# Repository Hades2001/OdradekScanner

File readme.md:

# Odradek Scanner
[中文](./readme_zh.md) | 英文

A 3D-printed Odradek Scanner project.

## Introduction

**Odradek Scanner** is a 3D-printed project inspired by the iconic scanner device.  
This repository is used to organize and publish the hardware resources, controller firmware, and related documentation required to build the project.

The goal of this project is not only to recreate its appearance, but also to turn it into a truly interactive Maker project that can be assembled, operated, and further expanded.

## Features

- Odradek-style 3D-printed structure
- Open-source hardware resources
- Controller firmware source code
- Project documentation including assembly manual and BOM
- Easy to organize, expand, and customize

## Repository Structure

.
├── Hardware/   # Open-source hardware files
├── Firmware/   # Controller firmware source code
├── Mechanical/ # Mechanical structure files
└── Docs/       # Assembly manual, BOM, and related documents

## Documentation

All project-related documentation will be organized in the `Docs/` directory, including:

* Assembly instructions
* BOM
* Wiring information
* User guide
* Additional reference materials

## Open Source

This project will continue to be organized and shared as an open-source Maker project.  
You are welcome to study it, build it, modify it, and further improve or expand it.

## Contribution

Suggestions, improvements, and additional content are always welcome.  
If you build your own version or improve the project, feel free to share your work.

## License

* [Hardware: CERN-OHL-P-2.0](./LICENSE/LICENSE-CERN-OHL-P-2.0.txt)
* [Firmware: MIT](./LICENSE/LICENSE-MIT.txt)
* [Documentation: CC BY 4.0](./LICENSE/LICENSE-CC-BY-4.0.txt)

## Notes

This repository will continue to be updated and expanded over time, with more files and documentation added gradually.

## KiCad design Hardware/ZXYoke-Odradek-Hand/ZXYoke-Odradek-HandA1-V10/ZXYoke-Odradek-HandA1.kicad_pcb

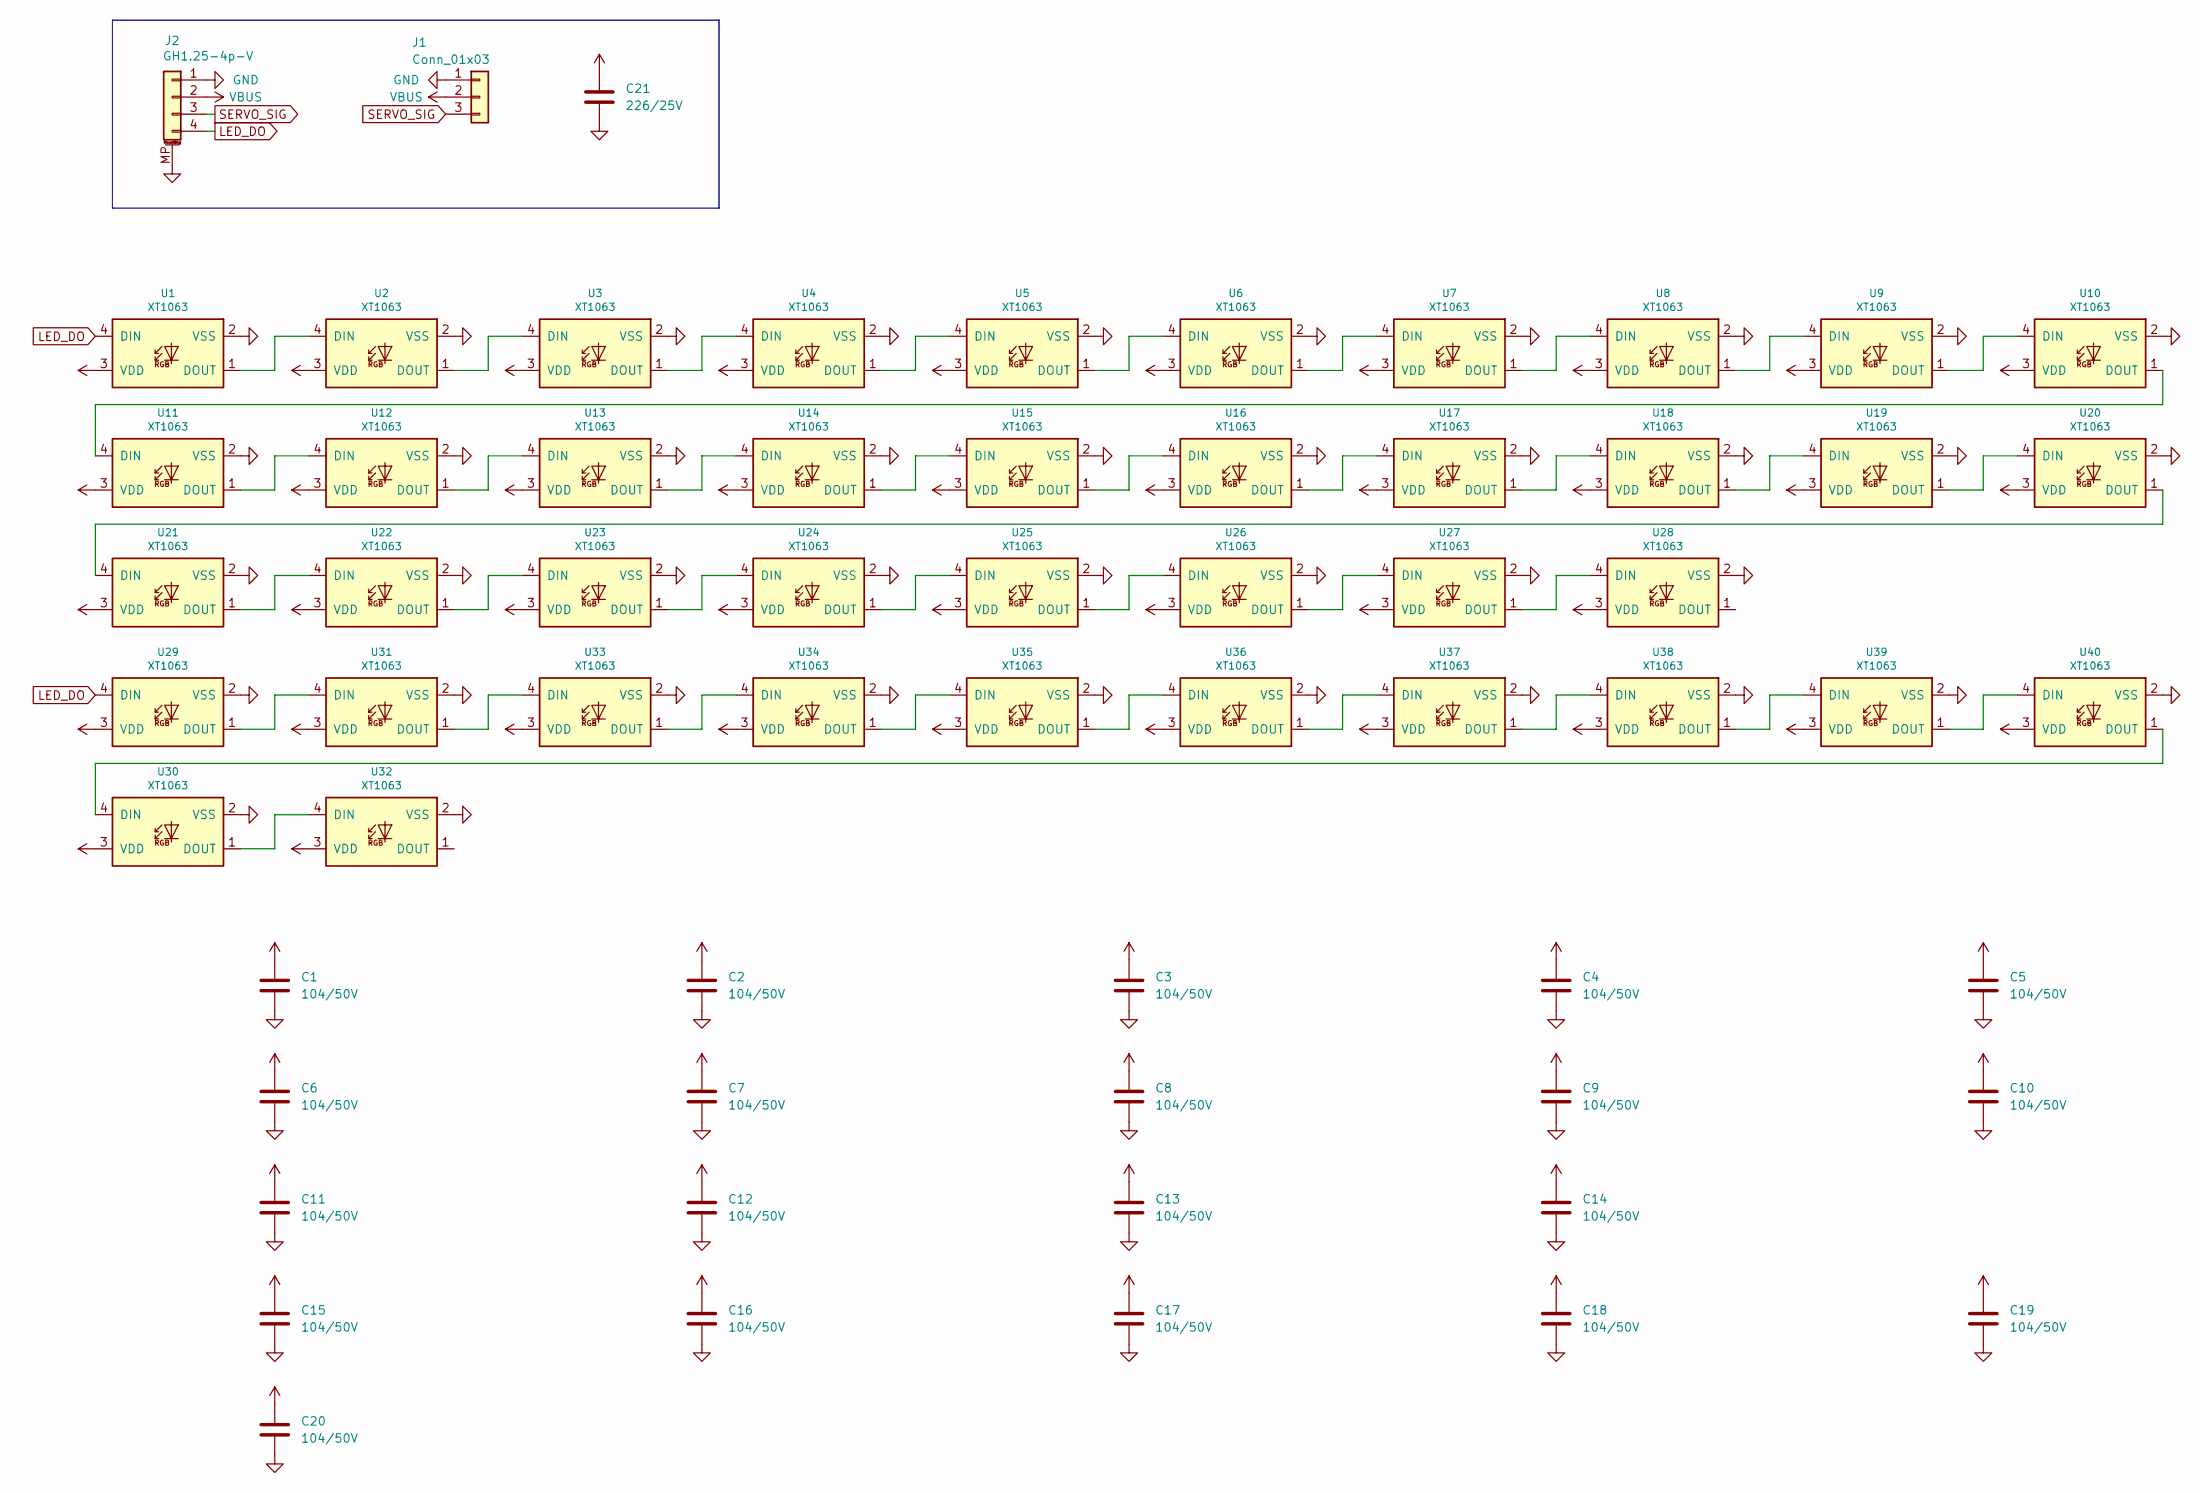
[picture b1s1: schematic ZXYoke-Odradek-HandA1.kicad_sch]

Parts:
C1, C2, C3, C4, C5, C6, C7, C8, C9, C10, C11, C12, C13, C14, C15, C16, C17, C18, C19, C20: 104/50V; C_0402_1005Metric
C21: 226/25V; C_0805_2012Metric
J1: Conn_01x03; PinHeader_1x03_P2.54mm_Horizontal
J2: GH1.25-4p-V; JST_GH_BM04B-GHS-TBT_1x04-1MP_P1.25mm_Vertical
U1, U2, U3, U4, U5, U6, U7, U8, U9, U10, U11, U12, U13, U14, U15, U16, U17, U18, U19, U20, U21, U22, U23, U24, U25, U26, U27, U28, U29, U30, U31, U32, U33, U34, U35, U36, U37, U38, U39, U40: XT1063

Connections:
GND: C1.2, C2.2, C3.2, C4.2, C5.2, C6.2, C7.2, C8.2, C9.2, C10.2, C11.2, C12.2, C13.2, C14.2, C15.2, C16.2, C17.2, C18.2, C19.2, C20.2, C21.2, J1.1, J2.1, J2.MP (MountPin), U1.2 (VSS), U2.2 (VSS), U3.2 (VSS), U4.2 (VSS), U5.2 (VSS), U6.2 (VSS), U7.2 (VSS), U8.2 (VSS), U9.2 (VSS), U10.2 (VSS), U11.2 (VSS), U12.2 (VSS), U13.2 (VSS), U14.2 (VSS), U15.2 (VSS), U16.2 (VSS), U17.2 (VSS), U18.2 (VSS), U19.2 (VSS), U20.2 (VSS), U21.2 (VSS), U22.2 (VSS), U23.2 (VSS), U24.2 (VSS), U25.2 (VSS), U26.2 (VSS), U27.2 (VSS), U28.2 (VSS), U29.2 (VSS), U30.2 (VSS), U31.2 (VSS), U32.2 (VSS), U33.2 (VSS), U34.2 (VSS), U35.2 (VSS), U36.2 (VSS), U37.2 (VSS), U38.2 (VSS), U39.2 (VSS), U40.2 (VSS)
LED_DO: J2.4, U1.4 (DIN), U29.4 (DIN)
unnamed: U1.1 (DOUT), U2.4 (DIN)
unnamed: U2.1 (DOUT), U3.4 (DIN)
unnamed: U3.1 (DOUT), U4.4 (DIN)
unnamed: U4.1 (DOUT), U5.4 (DIN)
unnamed: U5.1 (DOUT), U6.4 (DIN)
unnamed: U6.1 (DOUT), U7.4 (DIN)
unnamed: U7.1 (DOUT), U8.4 (DIN)
unnamed: U8.1 (DOUT), U9.4 (DIN)
unnamed: U9.1 (DOUT), U10.4 (DIN)
unnamed: U10.1 (DOUT), U11.4 (DIN)
unnamed: U11.1 (DOUT), U12.4 (DIN)
unnamed: U12.1 (DOUT), U13.4 (DIN)
unnamed: U13.1 (DOUT), U14.4 (DIN)
unnamed: U14.1 (DOUT), U15.4 (DIN)
unnamed: U15.1 (DOUT), U16.4 (DIN)
unnamed: U16.1 (DOUT), U17.4 (DIN)
unnamed: U17.1 (DOUT), U18.4 (DIN)
unnamed: U18.1 (DOUT), U19.4 (DIN)
unnamed: U19.1 (DOUT), U20.4 (DIN)
unnamed: U20.1 (DOUT), U21.4 (DIN)
unnamed: U21.1 (DOUT), U22.4 (DIN)
unnamed: U22.1 (DOUT), U23.4 (DIN)
unnamed: U23.1 (DOUT), U24.4 (DIN)
unnamed: U24.1 (DOUT), U25.4 (DIN)
unnamed: U25.1 (DOUT), U26.4 (DIN)
unnamed: U26.1 (DOUT), U27.4 (DIN)
unnamed: U27.1 (DOUT), U28.4 (DIN)
unnamed: U29.1 (DOUT), U31.4 (DIN)
unnamed: U30.4 (DIN), U40.1 (DOUT)
unnamed: U30.1 (DOUT), U32.4 (DIN)
unnamed: U31.1 (DOUT), U33.4 (DIN)
unnamed: U33.1 (DOUT), U34.4 (DIN)
unnamed: U34.1 (DOUT), U35.4 (DIN)
unnamed: U35.1 (DOUT), U36.4 (DIN)
unnamed: U36.1 (DOUT), U37.4 (DIN)
unnamed: U37.1 (DOUT), U38.4 (DIN)
unnamed: U38.1 (DOUT), U39.4 (DIN)
unnamed: U39.1 (DOUT), U40.4 (DIN)
SERVO_SIG: J1.3, J2.3
VBUS: C1.1, C2.1, C3.1, C4.1, C5.1, C6.1, C7.1, C8.1, C9.1, C10.1, C11.1, C12.1, C13.1, C14.1, C15.1, C16.1, C17.1, C18.1, C19.1, C20.1, C21.1, J1.2, J2.2, U1.3 (VDD), U2.3 (VDD), U3.3 (VDD), U4.3 (VDD), U5.3 (VDD), U6.3 (VDD), U7.3 (VDD), U8.3 (VDD), U9.3 (VDD), U10.3 (VDD), U11.3 (VDD), U12.3 (VDD), U13.3 (VDD), U14.3 (VDD), U15.3 (VDD), U16.3 (VDD), U17.3 (VDD), U18.3 (VDD), U19.3 (VDD), U20.3 (VDD), U21.3 (VDD), U22.3 (VDD), U23.3 (VDD), U24.3 (VDD), U25.3 (VDD), U26.3 (VDD), U27.3 (VDD), U28.3 (VDD), U29.3 (VDD), U30.3 (VDD), U31.3 (VDD), U32.3 (VDD), U33.3 (VDD), U34.3 (VDD), U35.3 (VDD), U36.3 (VDD), U37.3 (VDD), U38.3 (VDD), U39.3 (VDD), U40.3 (VDD)

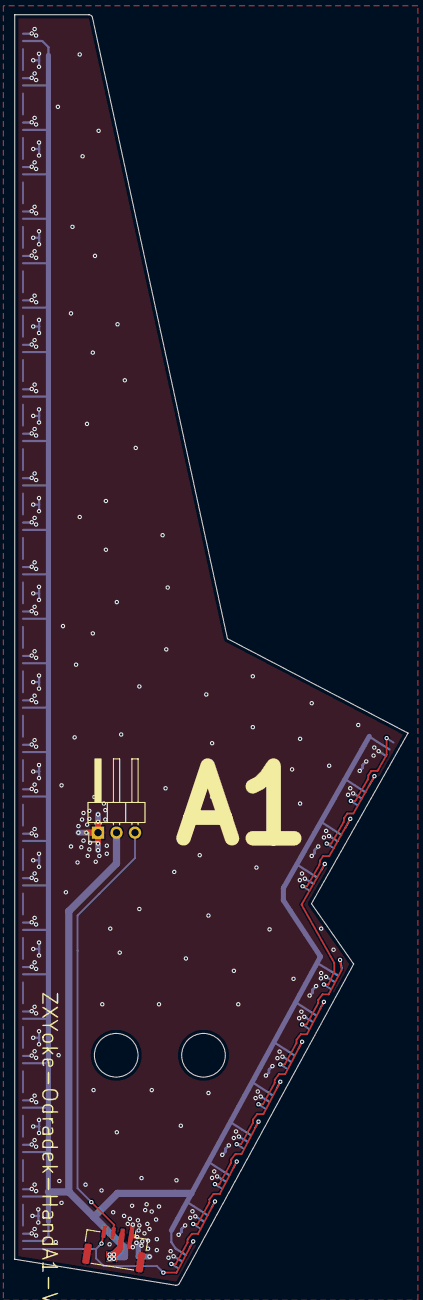
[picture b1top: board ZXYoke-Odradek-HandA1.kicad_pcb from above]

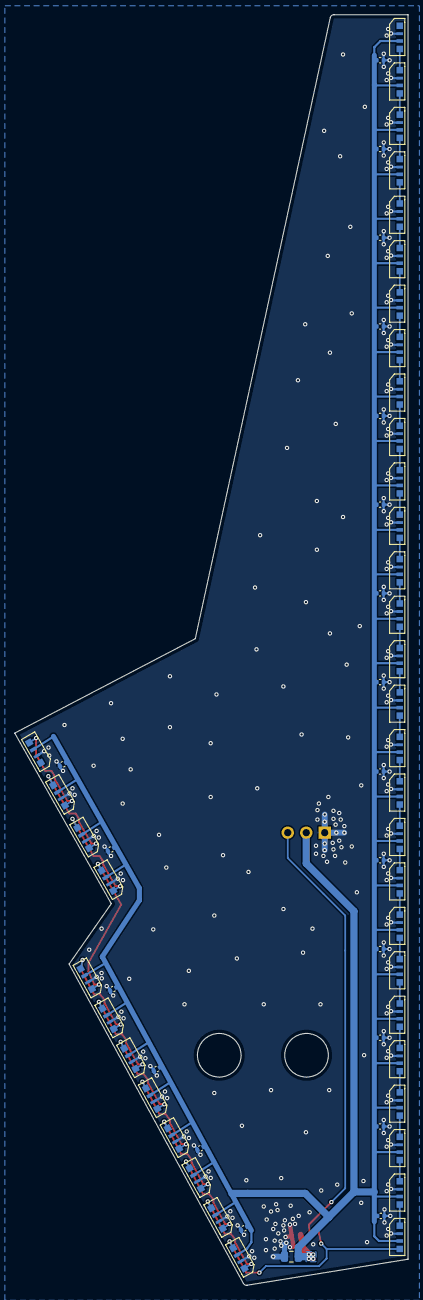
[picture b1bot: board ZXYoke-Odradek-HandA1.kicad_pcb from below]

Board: 2 copper layers, 54.1 x 174.7 mm, 63 parts (61 on the bottom side), 42 nets.

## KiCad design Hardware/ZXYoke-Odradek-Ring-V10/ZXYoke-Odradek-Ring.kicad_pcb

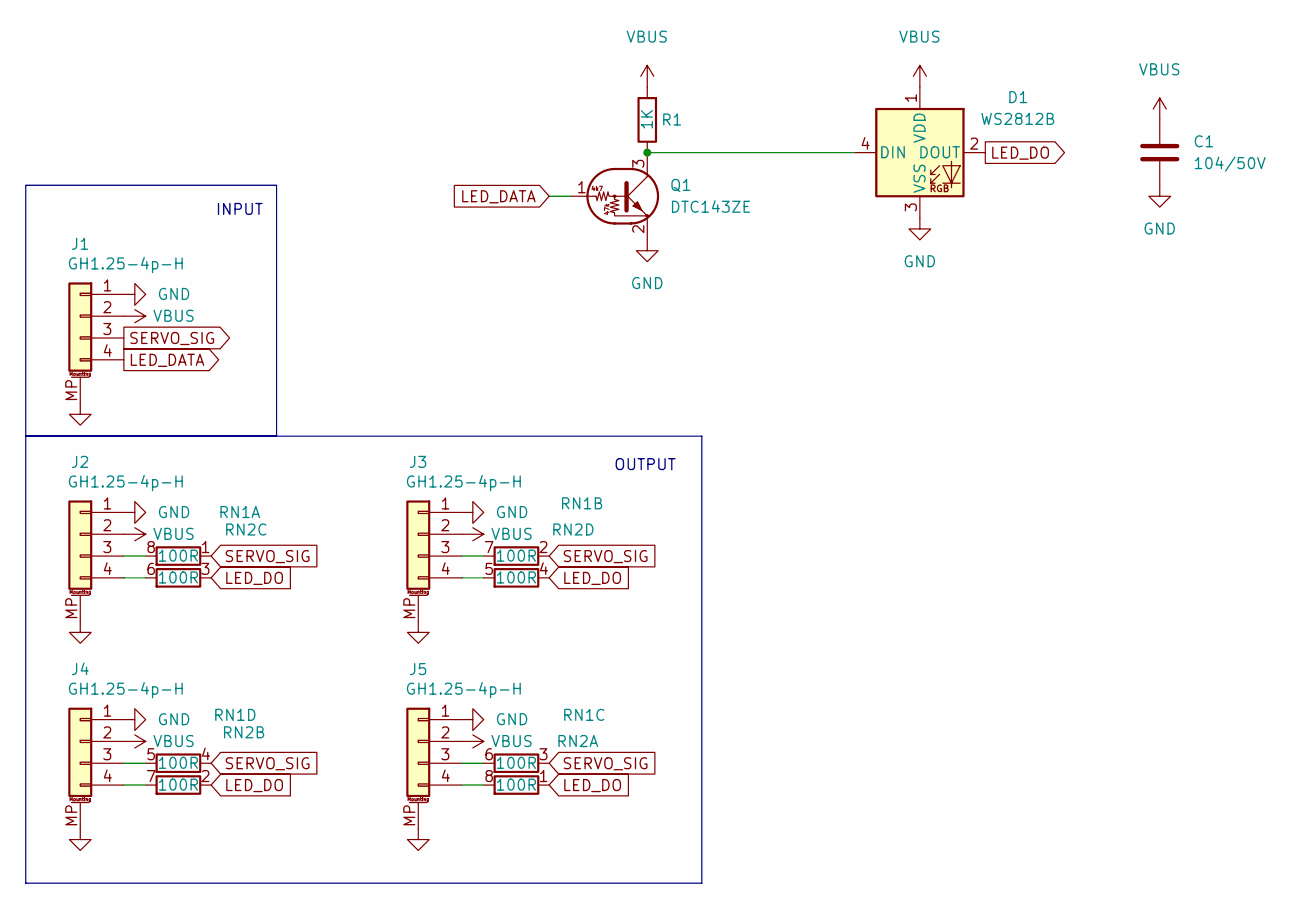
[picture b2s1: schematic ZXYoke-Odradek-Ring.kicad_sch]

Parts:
C1: 104/50V; C_0402_1005Metric
D1: WS2812B; LED_WS2812B_PLCC4_5.0x5.0mm_P3.2mm
J1, J2, J3, J4, J5: GH1.25-4p-H; JST_GH_SM04B-GHS-TB_1x04-1MP_P1.25mm_Horizontal
Q1: DTC143ZE; SOT-523
R1: 1K; R_0402_1005Metric
RN1, RN2: 100R; R_Array_Convex_4x0603

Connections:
GND: C1.2, D1.3 (VSS), J1.1, J1.MP (MountPin), J2.1, J2.MP (MountPin), J3.1, J3.MP (MountPin), J4.1, J4.MP (MountPin), J5.1, J5.MP (MountPin), Q1.2 (E)
LED_DATA: J1.4, Q1.1 (B)
LED_DO: D1.2 (DOUT), RN2.1 (R1.1), RN2.2 (R2.1), RN2.3 (R3.1), RN2.4 (R4.1)
unnamed: D1.4 (DIN), Q1.3 (C), R1.1
unnamed: J2.3, RN1.8 (R1.2)
unnamed: J2.4, RN2.6 (R3.2)
unnamed: J3.3, RN1.7 (R2.2)
unnamed: J3.4, RN2.5 (R4.2)
unnamed: J4.3, RN1.5 (R4.2)
unnamed: J4.4, RN2.7 (R2.2)
unnamed: J5.3, RN1.6 (R3.2)
unnamed: J5.4, RN2.8 (R1.2)
SERVO_SIG: J1.3, RN1.1 (R1.1), RN1.2 (R2.1), RN1.3 (R3.1), RN1.4 (R4.1)
VBUS: C1.1, D1.1 (VDD), J1.2, J2.2, J3.2, J4.2, J5.2, R1.2

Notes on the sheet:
OUTPUT
INPUT

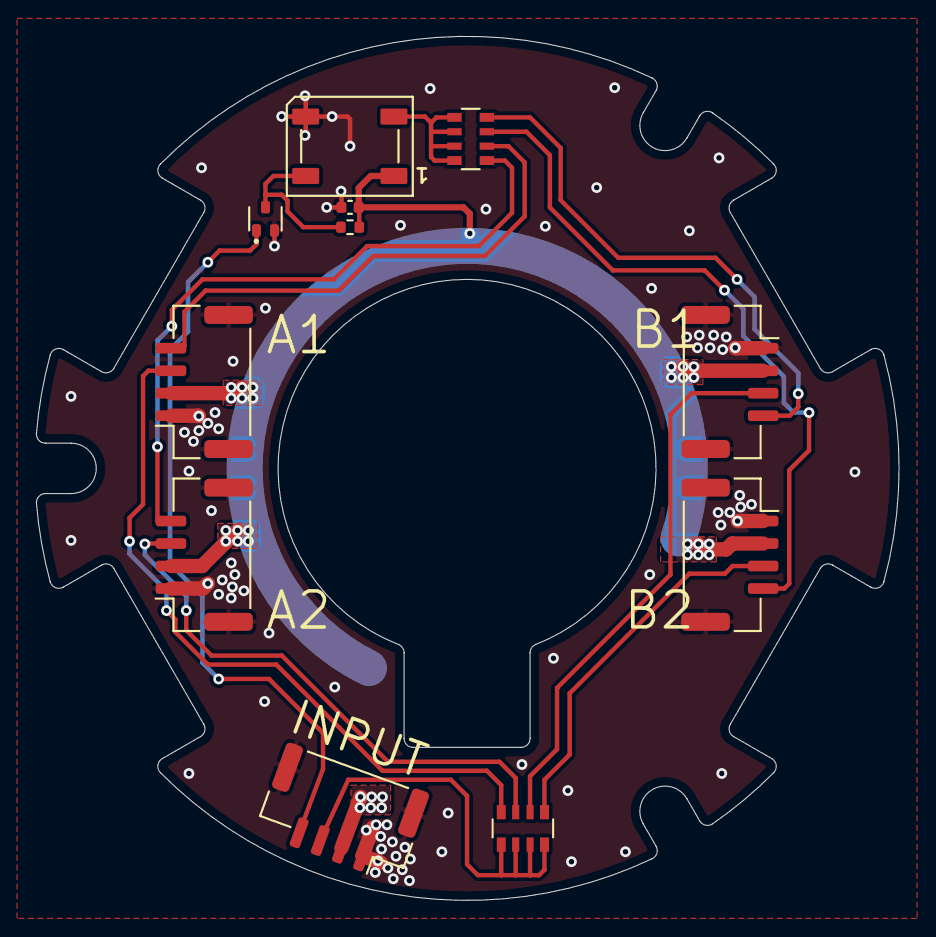
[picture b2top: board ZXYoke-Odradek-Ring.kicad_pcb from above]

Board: 2 copper layers, 47.9 x 48.0 mm, 11 parts (0 on the bottom side), 14 nets.

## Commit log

2026-05-08 creat this project
2026-05-08 add readme for Firmware/Hardware/Mechanical
2026-05-08 add Installation_Guide for English and updata Chinese version
2026-05-09 Add Hardware
    Added the PCB project files for four LED panels and the ring.
